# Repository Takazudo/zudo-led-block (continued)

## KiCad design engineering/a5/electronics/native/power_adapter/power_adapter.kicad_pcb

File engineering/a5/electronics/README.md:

# Light Block A5 — editable electronics checkpoint

This directory contains **three native KiCad 10 projects with complete schematics and part-to-pin connectivity**. The identical LED leaf and passive power adapter are routed and pass native PCB DRC. The controller contains the selected components and fixed interfaces, but **has no copper routing or planes and is not a manufacturing file**.

No hardware was assembled or tested during this work. Native software checks, ideal-circuit calculations, mechanical design intentions and physical qualification are kept distinct.

## Native project status

| Project | Fitted parts per board | Copies per module | PCB status |
|---|---:|---:|---|
| `native/controller/controller.kicad_pro` | 59 | 1 | Placement draft; **130 unconnected items**, two retained courtyard projection conflicts |
| `native/led_leaf/led_leaf.kicad_pro` | 10 | 2 | Routed; **0 DRC violations, 0 unconnected items** |
| `native/power_adapter/power_adapter.kicad_pro` | 2 | 1 | Routed; **0 DRC violations, 0 unconnected items** |

The controller's two reported violations are courtyard overlaps at J3–H1 and J3–C7. The native check reports no copper shorts, pad-clearance violations or copper-to-edge violations in the current placement. This does **not** qualify an unrouted board. All reports remain present without per-item exclusions or global suppression added to hide them. The package integration reports contain the separate native schematic ERC results and independent XML-netlist checks.

The fitted total is **30 manufacturer part types / 81 pieces per complete module**. Five bare SWD pads and mounting holes are not purchased parts. `fitted_component_ledger.json` gives every board-qualified reference designator and its C-code; it reconciles to the main A5 procurement ledger. A4.1 remains the historical baseline.

## What changed electrically from A4.1

The A4.1 passive CV-through path, 20 MΩ pickup, OPA197 buffer, 82 kΩ affine network, MCU and independent left/right LED data channels remain the circuit basis. A5 adds **U7 TLV9001IDBVR / C398363**, **R24 330 Ω / C23138**, **R25 1 kΩ / C21190** and **C17 100 nF / C14663**. These add four fitted pieces and one manufacturer type. A later mechanical correction removes controller J4 and adds a second SH4 to each identical leaf, a net **one additional C160404 connector**. Both original 50 mm completed SH4 cables remain in use.

U7 buffers the affine input before the MCU ADC. R24 and R25 form a nominal 100/133 divider and provide a defined low impedance to ground at the ADC. The input capacitor C13 is now **upstream of the existing R7**, on `CV_AFFINE`. R7 connects that filtered node to `CV_FILTER`, where the BAS70 clamp and U7 input connect. Thus the 10 nF capacitor cannot discharge directly into the U7 input clamp during a supply collapse. This uses the existing resistor and does not add R26.

The normal DC relationship is:

\[
V_{ADC}=\frac{100}{133}\left(\frac{V_{DD}}{2}+\frac{V_{CV}}{8}\right),
\qquad V_{CV}=10.64V_{ADC}-4V_{DD}.
\]

At 3.3 V, the nominal ADC values for −5 / 0 / +5 V are **0.77068 / 1.24060 / 1.71053 V**. The ideal affine network has a 20.5 kΩ Thevenin resistance, so the relocated 10 nF capacitor gives a nominal **776.37 Hz** pole. Firmware uses this A5 transfer explicitly; A4.1's unbuffered conversion settings must not be reused.

`reports/electrical_margins.json` is regenerated by `design/check_electrical_margins.py`. It checks 256 resistor combinations and two supply endpoints for each CV test input. This is an ideal resistor calculation, excluding op-amp error, ADC/reference error, leakage, temperature coefficients and ageing.

### Scope of the power-off improvement

Two bounded calculations are useful, but neither is a blanket power-sequencing approval:

* With CV in ±5 V, initial VDD between 3.0 and 3.6 V, and 1% resistor corners, maximum C13 precharge is about **2.44335 V**. R7 is at least 990 Ω. If its receiving node remains at or above −0.5 V, that capacitor path is limited to **2.974 mA**, below the TLV9001's stated 10 mA over-rail input-current condition.
* For a steady-DC scenario with no other stored or supplied energy reaching the ADC, a deliberately conservative `|CV_BUF| ≤ 20 V` source through R3 ≥81.18 kΩ supplies at most 246.37 µA. Assigning all of it to R25 ≤1.01 kΩ gives **|VADC| ≤0.24883 V**; including R7 tightens the bound. This does not assume that an unpowered TLV9001 has a specified output voltage.

The remaining gates are explicit: **partial supplies, U7's differential-input absolute maximum, all transient energy paths, regulator reverse current, ESD and rail overshoot have not been qualified**. The 1 kΩ shunts and revised capacitor placement improve defined paths; they do not establish unspecified semiconductor behavior. TI specifies the TLV9001's over-rail current condition and a separate differential-input limit; both matter. ST's ADC voltage limits cannot be replaced by an injection-current-only argument. Sources: [TI TLV9001](https://www.ti.com/lit/ds/symlink/tlv9001.pdf), [ST STM32G031](https://www.st.com/resource/en/datasheet/stm32g031f8.pdf).

## Fixed hardware interfaces

| STM32 UFQFPN28 pin | Signal | Behavior |
|---:|---|---|
| 3 / 4 | VDD / VSS | 3.3 V / ground |
| 5 | PF2 / NRST | 10 kΩ pull-up and 100 nF to ground |
| 6 | PA0 / ADC_IN0 | Buffered and divided CV input |
| 8 / 9 | PA2 / PA3 | Active-low switch throws, external 10 kΩ pull-ups |
| 10 | PA4 | Active-low LED `/FAULT` |
| 11 | PA5 | **High enables** VLED through the NPN |
| 12 / 13 | PA6 / PA7 | AF1 TIM3 CH1 / CH2, independent LED streams |
| 20 / 21 | PA13 / PA14 | SWDIO / SWCLK |

Switch common pin 2 is grounded. `(MODE_A, MODE_B)` is 01 ON, 11 PROGRAM, 10 CV, 00 invalid. The actual installed lever direction still requires the incoming switch continuity check.

The SWD row is on the **rear face at local Y32.2 / global Y80.7**. In increasing PCB X, it is **3V3 sense, GND, SWDIO, SWCLK, NRST**. The probe must not back-power the board. Removing the second controller header freed this access area and removed the earlier switch-body obstruction. Fixture approach and optical/harness removal still require mechanical qualification; it is not a claim of unobstructed field access in a fully assembled module.

**CV IN and THRU are passive copper connections in the schematic.** PJ-3582 pin 6 is the tip; both tips share `CV_THRU`. Pin 2 is sleeve and pin 3 ring, both grounded for this mono CV use. Insertion-detect contacts 4 and 5 are unused. Connector drawing interpretation is independently checked, but incoming contact continuity remains a factory gate. The controller PCB must still route that passive connection.

**Both independent LED streams share one controller SH4 and continue through the identical leaves.** They are not serialized into one eight-LED chain. The cables are straight 1:1 and use this exact mapping:

| Physical connector | Pin 1 | Pin 2 | Pin 3 | Pin 4 |
|---|---|---|---|---|
| Controller J3 | GND | VLED | DATA_L | DATA_R |
| Left leaf J1 | GND | VLED | Left leaf DIN | Right stream through |
| Left leaf J2 | GND | VLED | Right stream through | Left stream stub |
| Right leaf J1 | GND | VLED | Right leaf DIN | Left stream stub |
| Right leaf J2, unused externally | GND | VLED | Left stream stub | Right stream stub |

Cable 1 connects controller J3 to left J1. Cable 2 connects left J2 to right J1. On either identical leaf, J1 pins 3/4 are `DATA_IN` / `DATA_OTHER`, and J2 swaps them. Pin 4 is active in this revision. This is a custom assignment, not a Qwiic interface. The right board is flipped end-for-end, reversing its physical pixel order. Uniform-per-chain firmware is unaffected; future spatial patterns must account for this mapping.

The first SH4 cable now carries both leaves' current. JST specifies 1.0 A with AWG28, versus the TPS limit maximum of about 0.439 A. The linked Adafruit drawing specifies AWG28; current delivered construction remains an incoming-lot check. At that current, an ideal 35 µm copper calculation for the first leaf's 0.5 mm rails and 0.35 mm connector branches gives about **59 mV loop drop and 26 mW loss** through the bridge path. This excludes contacts, cable resistance, copper tolerance, temperature and transients; it is not a thermal qualification. Sources: [JST SH](https://www.jst-mfg.com/product/pdf/eng/eSH.pdf), [Adafruit linked cable drawing](https://cdn-shop.adafruit.com/product-files/4399/C14172-001_Kaweei_CBH-100-04-050-A.pdf).

The power cable is Molex 151340300, whose endpoints reverse pins 1 and 3. Accordingly, controller J5 is **1 +12 / 2 GND / 3 −12**, while adapter J2 is **1 −12 / 2 GND / 3 +12**. The IDC connector is **pins 1–2 −12 (red stripe), 3–8 GND, 9–10 +12**. The adapter's copper deliberately compensates the completed cable's reversal.

## Protection and LED behavior

D1's anode faces raw +12 V and its cathode feeds protected +12 V. D2's cathode faces raw −12 V and its anode feeds protected −12 V. These are the intended opposite series-diode polarities for the bipolar supply; actual reverse-connection and partial-rail tests remain required.

The AP63205 produces the unswitched 5 V rail. The TPS2552DBVR-1 is the **active-low, overcurrent latch-off variant**. Its EN pin is pulled up to unswitched 5 V, so VLED defaults off. PA5 high drives an NPN that pulls EN low. The NPN has a base pull-down. The 68 kΩ, 1% ILIM resistor gives the manufacturer-equation range **343.3–439.4 mA**, nominal **388.1 mA**. This is an electrical protection threshold, not a permissible enclosure heat load.

Toggling EN or removing input power clears the hardware overcurrent latch. Firmware therefore records an armed/fault state before enabling and inhibits ordinary warm-reset retries. The TPS family also has thermal behavior that must not be confused with a permanent thermal latch. Firmware brightness/thermal PWM policy remains separate from current protection. Source: [TI TPS2552 family](https://www.ti.com/lit/ds/symlink/tps2552.pdf).

The SN74LVC2T45 uses VCCA=3.3 V, VCCB=switched VLED, and DIR tied to VCCA. Input and output pull-downs give defined idle levels; the manufacturer's Ioff/isolation behavior supports the intended supply sequencing. Measured startup, shutdown and data behavior still belongs in prototype qualification. Source: [TI SN74LVC2T45](https://www.ti.com/lit/ds/symlink/sn74lvc2t45.pdf).

The exact Worldsemi manufacturer file currently has footer **V1.4**, even though its URL ends `v6-1.0.pdf`. Its T1-low range differs from an older distributor copy. Firmware uses the current table and a 60 MHz timer with 78 ticks per cell, 21 ticks high for zero and 57 for one, with a 320 µs reset tail. Verify the incoming LED lot and the actual waveform. The chosen LED remains a Standard PCBA part with MSL handling requirements. Source: [Worldsemi WS2812B-2020-V6](https://www.world-semi.com/downloads/datasheets/en/ws2812b-2020-v6-1.0.pdf).

## Mechanical and board details

The controller is 8.8 ×62.9 ×1.6 mm; global Y48.5–111.4, front Z12.6. Its only LED connector J3 has final origin global **Y60.5**, opening toward −Y. Controller J4 is absent. The adapter is 8.8 ×30 ×1.6 mm, global Y18–48, front Z17.4. Its IDC pin-array center is Y33.4 and PicoBlade pin row Y46.7.

Each leaf is **9.0 ×82.5 ×0.6 mm**, with LEDs at local Y3.75, 28.75, 53.75 and 78.75. Both SH4s face +local Y, with origins at Y16.5 and Y66.0. Two symmetric front-edge notches, X0–1 mm and Y23.2–25.2 /57.3–59.3, clear the adapter tail geometry in either flipped orientation. The power rail detours around both notches. Internal-corner cutter radius and board fabrication tolerances require factory review; the mechanical scenario uses a maximum 0.5 mm internal radius.

Some controller courtyard projections are deliberate design intentions, **not DRC exclusions**:

* J3 projects into the rear M2 keepout. The mechanical model puts the nut at Z15.4–17.0, above an insulating PETG clamp, with a local pad pocket. Solder height and clamp clearance remain gates.
* J3's rectangular courtyard intersects C7's courtyard; their nominal molded-body projections are separated by about 0.825 mm. Check the actual mated plug, wire bend and clamp relief, not just library rectangles.

The former J4 mated-plug conflict with the toggle tail and D3 is **resolved in the current topology by removing J4**. The new bridge cable follows the mechanical model around the front of the leaves; its 1.5–1.75 mm design bend radius and actual completed-cable fit remain sample gates. Four resistors and the SWD row now occupy the freed rear area, so no under-switch part placement is required. Switch slots were increased to **1.8 ×1.2 mm with 2.3 ×1.7 mm pads**, providing a nominal 0.25 mm annulus, because the earlier 1.6 ×1.0 mm oval did not contain the rectangular terminal's corners with tolerance.

The controller still needs routing, local bypass optimization, grounded return paths and full power-loop review. The buck input capacitor, switch node, bootstrap loop and feedback return must be treated as a compact power circuit. C3's present placement and the remote bypass/ILIM placements require attention before routing is called final. The selected Samsung MLCCs have nominal capacitance margin, but **effective capacitance versus DC bias, temperature, tolerance and ageing is not proven**. No unsupported minimum-capacitance value is asserted. The TDK inductor is the active `SPM4020T-4R7M-LR`; its typical saturation rating does not by itself close the AP63205 hot-fault requirement. Sources: [Diodes AP63205](https://www.diodes.com/assets/Datasheets/AP63200-AP63201-AP63203-AP63205.pdf), [TDK SPM4020-LR](https://product.tdk.com/system/files/dam/doc/product/inductor/inductor/smd/catalog/inductor_commercial_power_spm4020-lr_en.pdf).

## Reproduction and evidence

Open any native `.kicad_pro` with **KiCad 10**. Symbols and footprints are supplied locally; no global library installation is required for editing, ERC or DRC. Optional upstream package 3D models are not bundled; the separate mechanical assembly is the current component-envelope study. KiCad's licensed upstream footprint sources and license are in `footprints/upstream/`. Manufacturer source URLs, document hashes, drawing pages and extracted design facts are listed in `source_provenance.json`; the package does not require redistributed manufacturer PDFs. The historical Würth inductor alternative is not a drop-in claim for this TDK land pattern. The assembly process must also reconcile TDK's no-cleaning guidance with leakage control around the20MΩ CV pickup.

To regenerate with KiCad's Python module available:

```sh
python3 design/generate_electronics.py
./validate_native.sh
```

Set `KICAD_CLI` if the executable is not on PATH. A portable extracted KiCad may additionally require its own per-process library/data/Python paths. Those environment paths are intentionally not hard-coded into the deliverable. `design/place_controller.py` is an exploratory packer that writes a separate experiment file, **not the authoritative placement**; the reviewed overrides are `design/controller_placement_override.json`. Native regeneration can assign new internal UUIDs, so rerun verification and refresh the SHA snapshot afterward.

The authoritative exact-file record is **`reports/pcb_qualification.json`**. It binds each board, project rule file, DRC report and footprint source to SHA-256 hashes. `placement_and_connectivity.json` records exact native pad centers, board sides, component poses and nominal body envelopes; the native boards remain the authority for actual copper geometry.

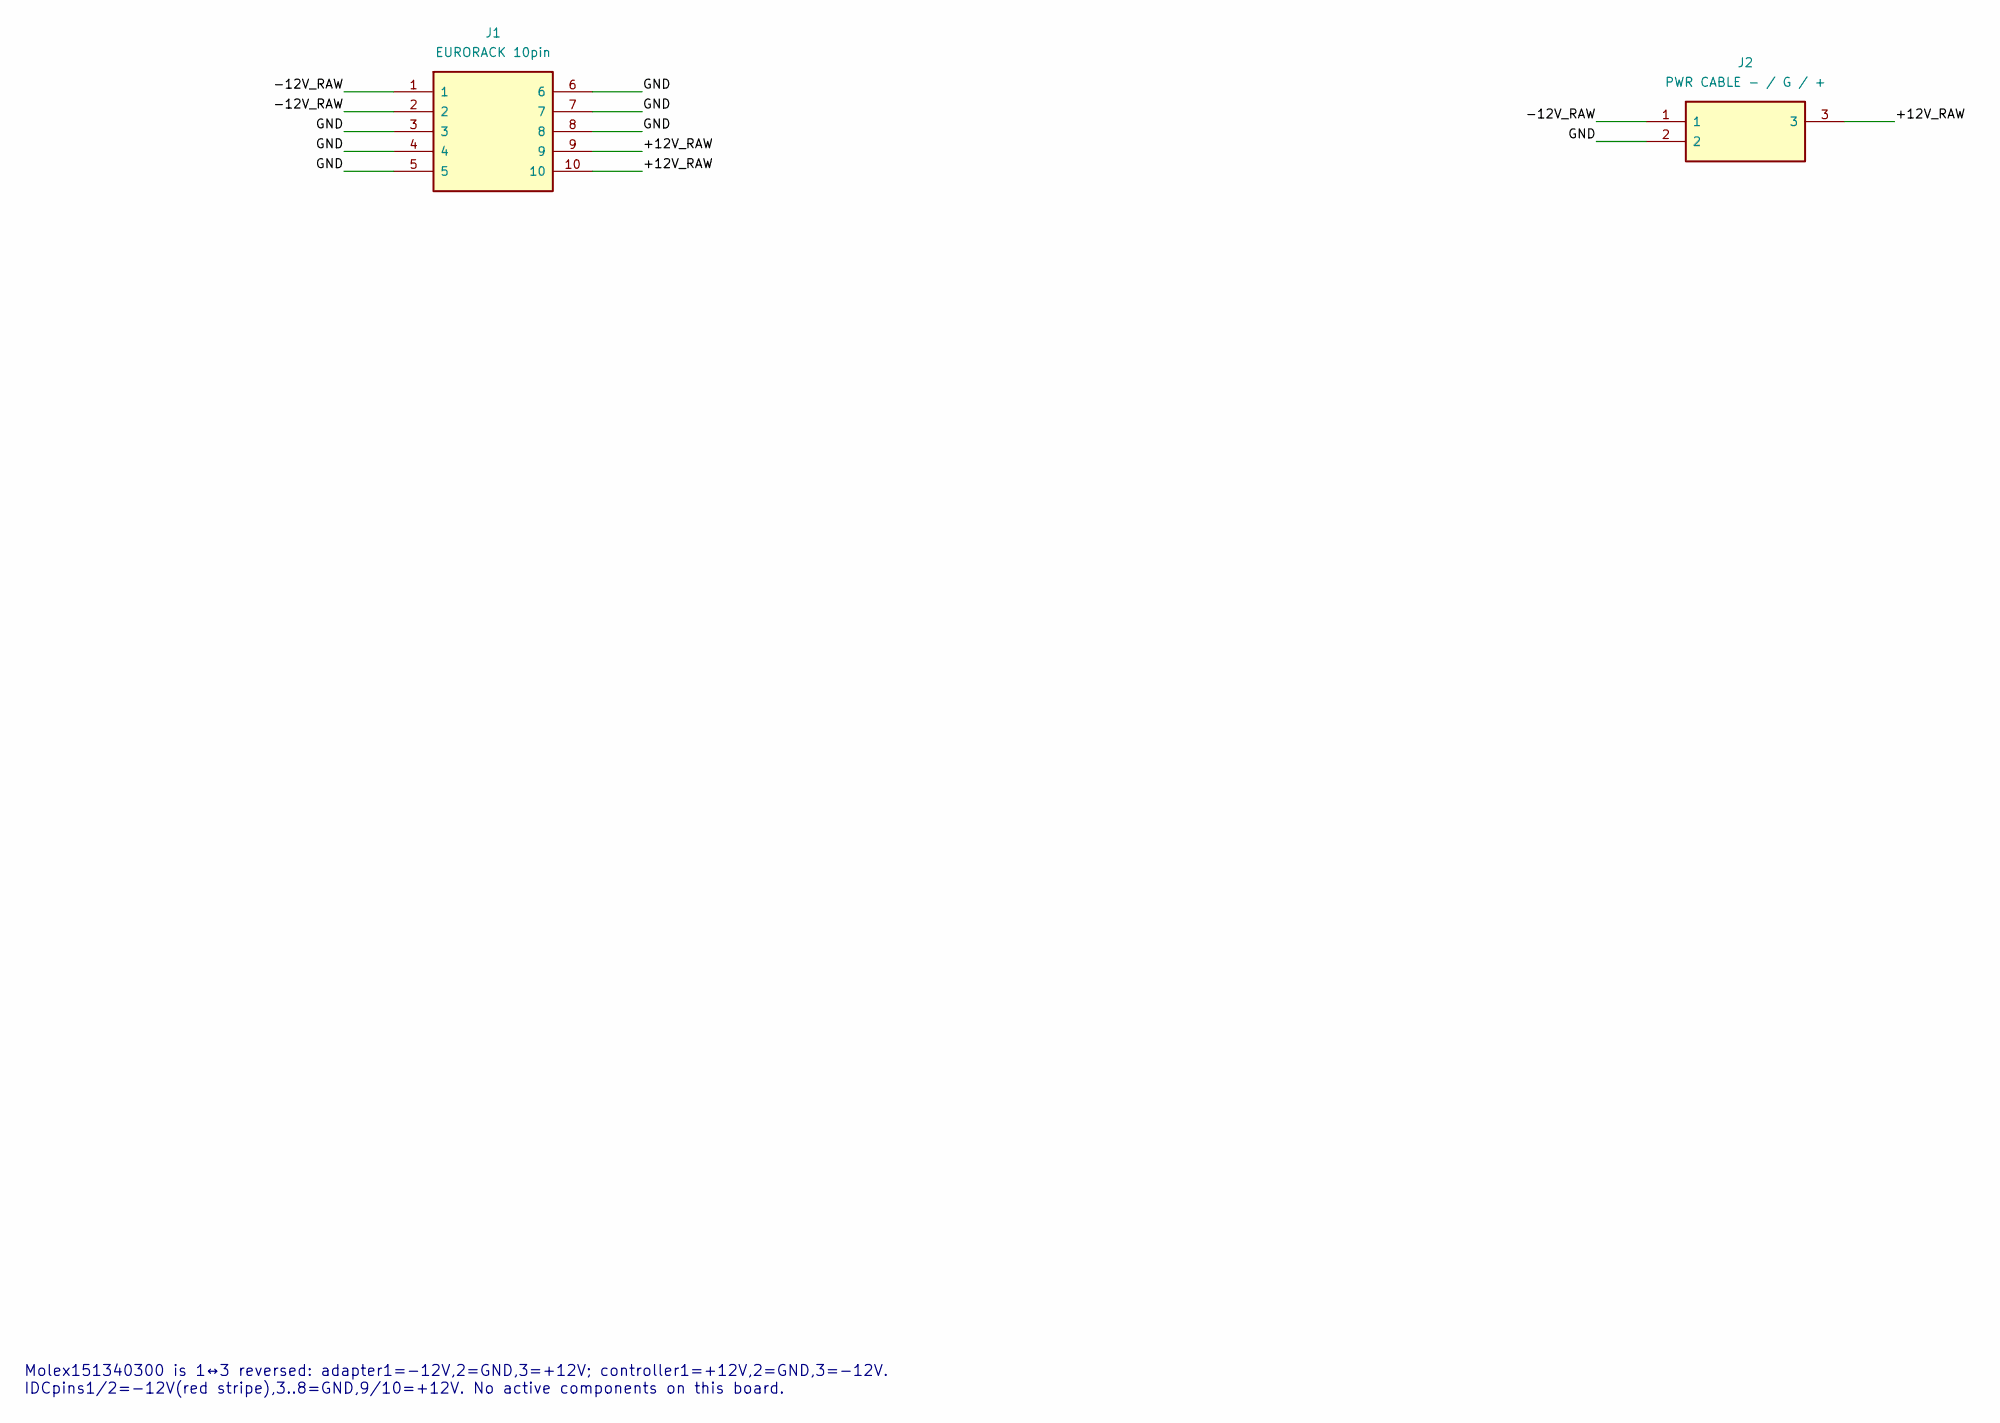
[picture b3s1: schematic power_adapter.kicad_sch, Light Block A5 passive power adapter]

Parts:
J1: EURORACK 10pin; IDC10; MPN 2.54-2*5P; LCSC C5665
J2: PWR CABLE - / G / +; PICO3; MPN 530470310; LCSC C122442

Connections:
+12V_RAW: J1.9, J1.10, J2.3
-12V_RAW: J1.1, J1.2, J2.1
GND: J1.3, J1.4, J1.5, J1.6, J1.7, J1.8, J2.2

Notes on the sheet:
Molex151340300 is 1↔3 reversed: adapter1=-12V,2=GND,3=+12V; controller1=+12V,2=GND,3=-12V. IDCpins1/2=-12V(red stripe),3..8=GND,9/10=+12V. No active components on this board.

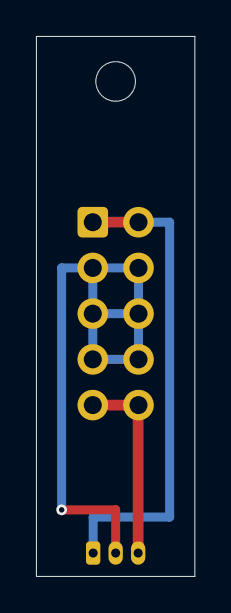
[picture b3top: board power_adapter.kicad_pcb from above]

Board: 2 copper layers, 8.8 x 30.0 mm, 3 parts (0 on the bottom side), 3 nets.

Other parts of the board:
H1: M2 NPTH
